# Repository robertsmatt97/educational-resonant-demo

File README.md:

# Educational Demos for Resonant Converter Phenomena

This repository stores all of the project files corresponding to the paper published under the same name. The files are necessary for building, simulating, and operating the converter described in the paper.

## Navigating the Project Files

1. User Manual
    - A detailed guide for setting up and operating the educational board.
    - The User Manual is listed already in the published paper but will be regularly updated here.
    
2. Bill of Materials
    - An Excel spreadsheet that contains every component used for the educational converter.
    - URLs, part numbers, and prices are listed.
    - Mouser cart link attached (To be added) is at the bottom of the spreadsheet for easy purchasing.
    - It is recommended to buy extra parts.
    
3. GERBER Files Zip File
    - A zip file for PCB manufacturers for convenient PCB purchasing.
    - The zip file is suitable for Smart Prototyping, which was used to create the prototype.
    - Some PCB manufacturers require different export options. The User Manual describes how to export it correctly.
    
4. "Videos" Folder
    - Videos demonstrating the capabilities of the converter. 
    - YouTube links are listed below as well. (To be added)
    - Demonstration 1: (To be added)
    - Demonstration 2: (To be added)
    
5. "KiCAD" Folder
    - KiCAD project files containing the schematic and PCB of the converter.
    - Library paths may need to be configured to see symbols and footprints correctly.
    
6. "MATLAB" Folder
    - MATLAB scripts to show hypothetical, simulation, and converter data over different combinations of resonant converter design parameters.
    - 'Resonant_Design.m' shows hypothetical and simulation data only. The board does not need to be connected.
    - 'Resonant_Design_Serial.m' shows hypothetical, simulation, and converter data. The board needs to be connected, and the CCS script needs to be running.
    - MATLAB 2019b or higher is required to run the 'Resonant_Design_Serial.m' script. 
    
7. "LTSpice" Folder
    - Simulation files for the resonant converter. 
    - Configure the parameters where it is listed.
    - Follow the User Manual for instructions on additional operation.
    
8. "CCS" Folder
    - Code Composer Studio (CCS) project files containing the code needed for operation. 
    - The latest version of CCS is recommended for the converter to work.

## To-Do List

1. Add Mouser Cart link of all the components. 
2. Add YouTube links of video demonstrations.
3. Add more visuals to User Manual.
3. Add additional microcontroller features to shorten downtime for demonstrations.

## Contact Information for Help

You can contact me at my email below for assistance in getting the board to work. Please be detailed in your issues.
Email: robertsmatt97@gmail.com

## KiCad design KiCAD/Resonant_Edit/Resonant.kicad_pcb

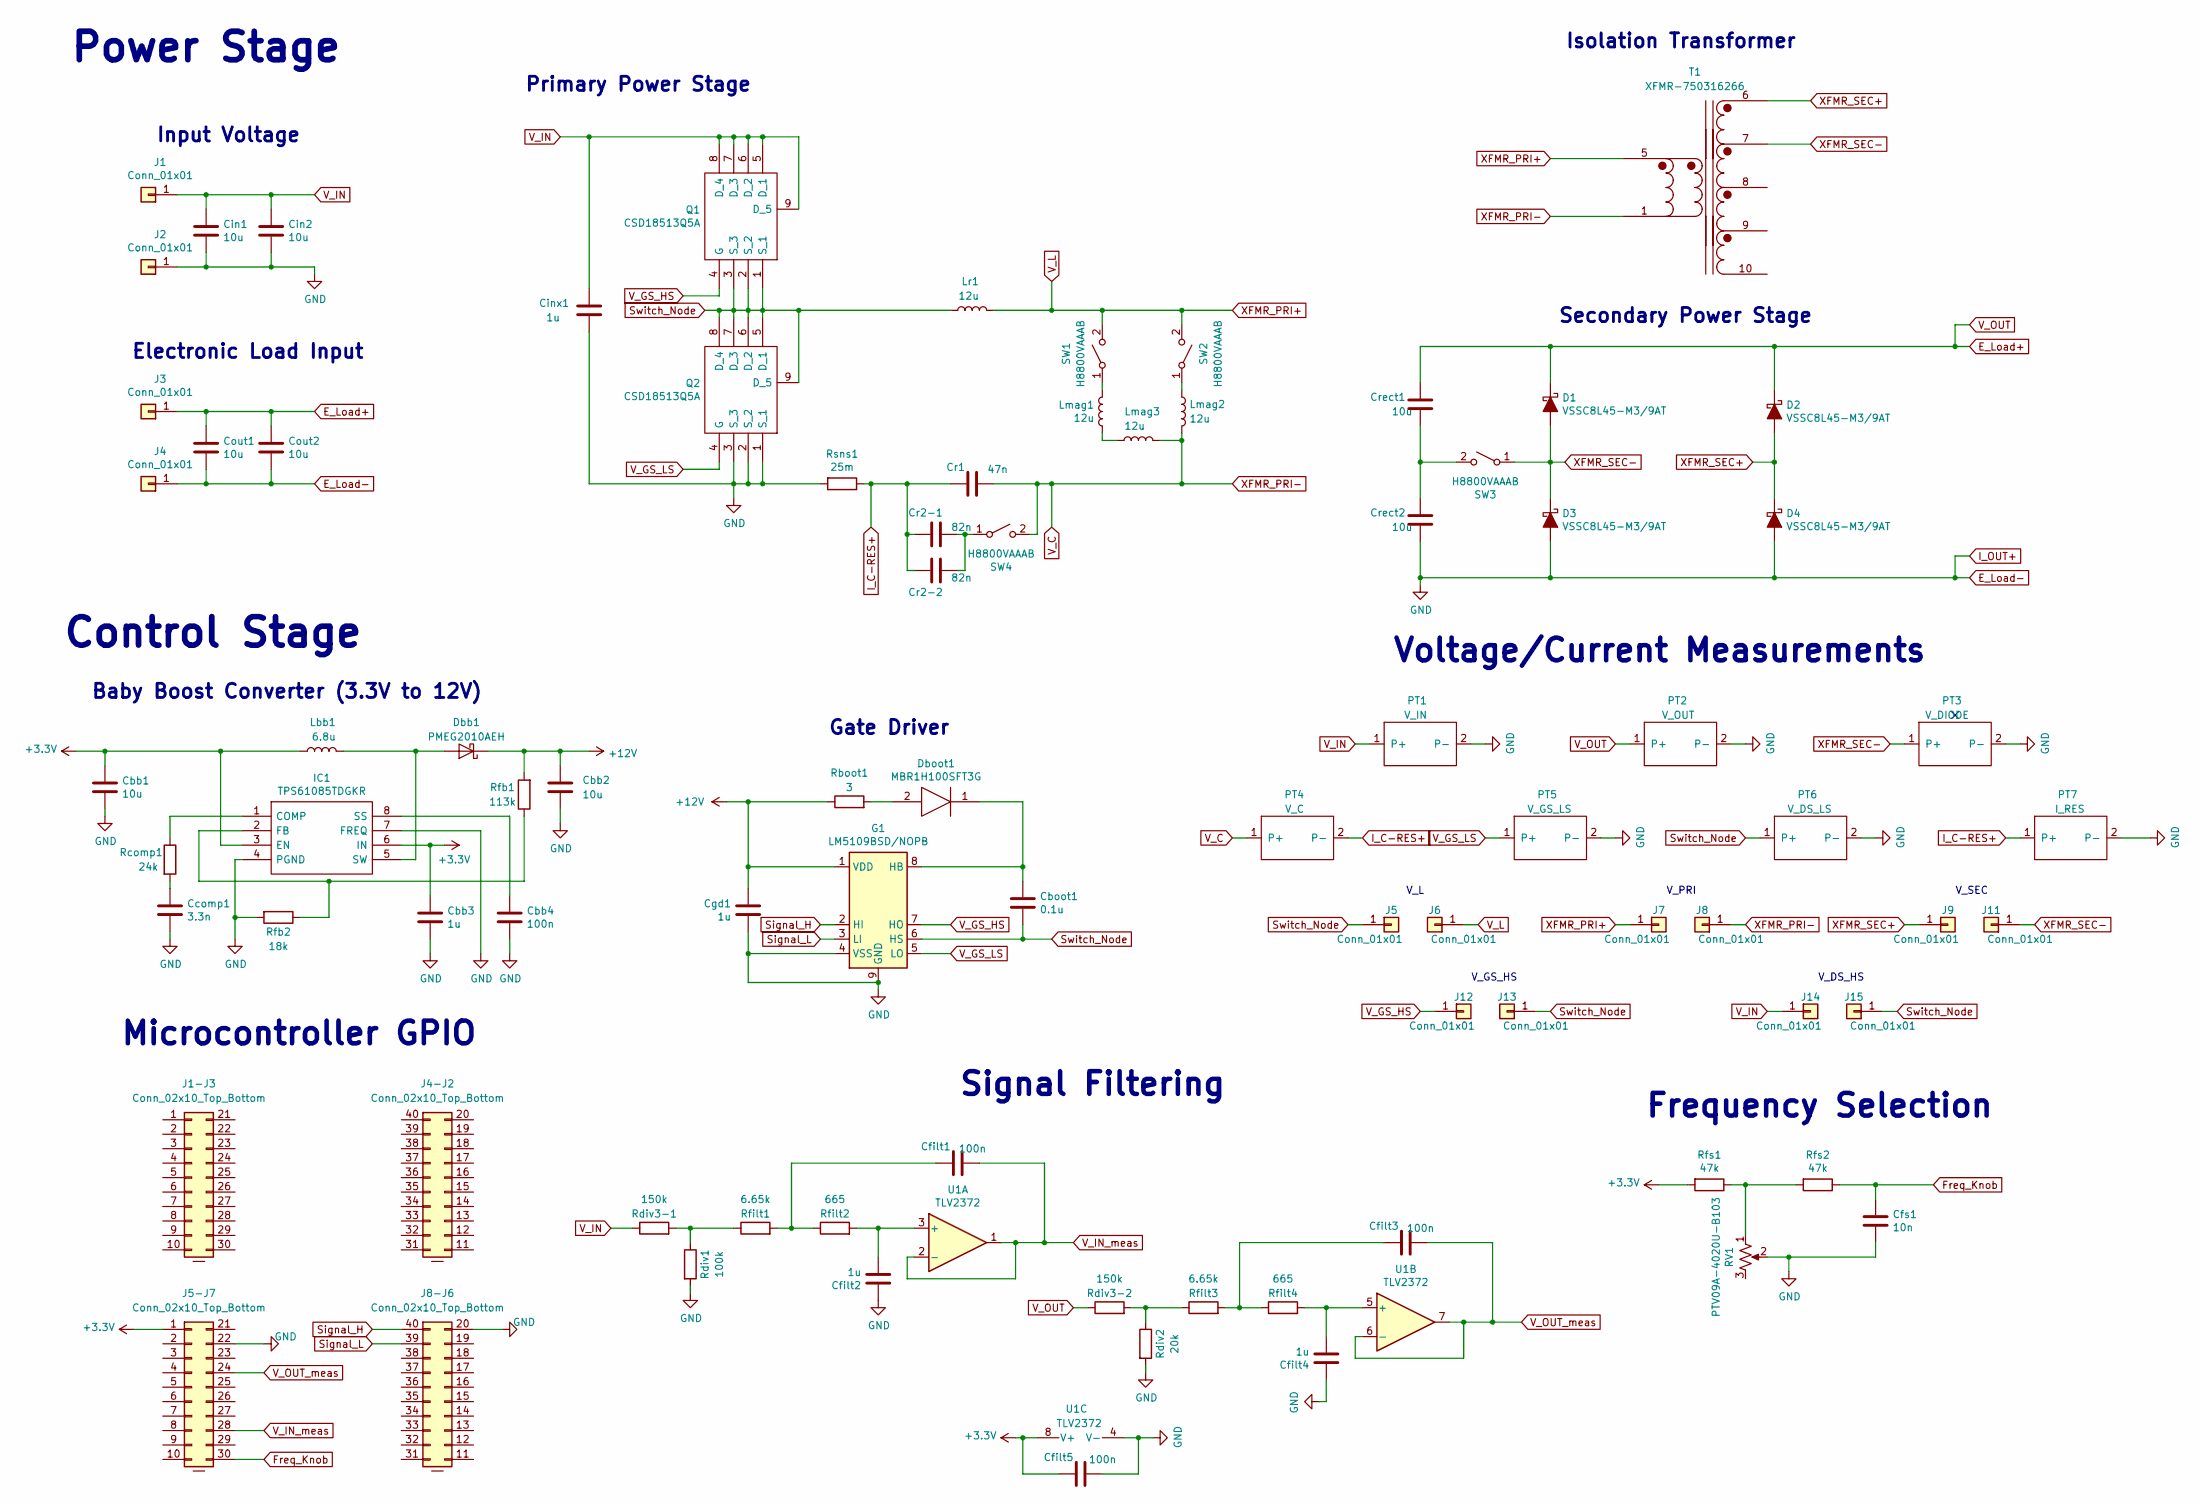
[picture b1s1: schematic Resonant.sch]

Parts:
Cbb1, Cbb2: 10u; C_0603_1608Metric
Cbb3: 1u; C_0603_1608Metric
Cbb4: 100n; C_0603_1608Metric
Cboot1: 0.1u; C_0603_1608Metric
Ccomp1: 3.3n; C_0805_2012Metric
Cfilt1, Cfilt3, Cfilt5: 100n; C_0603_1608Metric
Cfilt2, Cfilt4: 1u; C_0603_1608Metric
Cfs1: 10n; C_0603_1608Metric
Cgd1: 1u; C_0603_1608Metric
Cin1, Cin2: 10u; C_0603_1608Metric
Cinx1: 1u; LLL31MR71C105MA01L
Cout1, Cout2: 10u; C_0603_1608Metric
Cr1: 47n; C_0805_2012Metric
Cr2-1, Cr2-2: 82n; C_1206_3216Metric
Crect1, Crect2: 10u; C_0603_1608Metric
D1, D2, D3, D4: VSSC8L45-M3/9AT; VSSC8L45-M3_9AT
Dbb1: PMEG2010AEH; D_SOD-123
Dboot1: MBR1H100SFT3G; Mouser Part Number 863-MBR1H100SFT3G
G1: LM5109BSD/NOPB; LM5109BSD_NOPB
IC1: TPS61085TDGKR; Mouser Part Number 595-TPS61085TDGKR
J1, J2, J3, J4, J5, J6, J7, J8, J9, J11, J12, J13, J14, J15: Conn_01x01; PinHeader_1x01_P2.54mm_Vertical
J1-J3, J5-J7: Conn_02x10_Top_Bottom; 90151-2320_J1
J4-J2, J8-J6: Conn_02x10_Top_Bottom; 90151-2320_J2
Lbb1: 6.8u; L_0805_2012Metric
Lmag1, Lmag2, Lmag3: 12u; 744373965120
Lr1: 12u; 744373965120
PT1: V_IN; Probe_Test
PT2: V_OUT; Probe_Test
PT3: V_DIODE; Probe_Test
PT4: V_C; Probe_Test
PT5: V_GS_LS; Probe_Test
PT6: V_DS_LS; Probe_Test
PT7: I_RES; Probe_Test
Q1, Q2: CSD18513Q5A; Mouser Part Number 595-CSD18513Q5A
RV1: PTV09A-4020U-B103
Rboot1: 3; R_0603_1608Metric
Rcomp1: 24k; R_0603_1608Metric
Rdiv1: 100k; R_0603_1608Metric
Rdiv2: 20k; R_0603_1608Metric
Rdiv3-1, Rdiv3-2: 150k; R_0603_1608Metric
Rfb1: 113k; R_0805_2012Metric
Rfb2: 18k; R_0805_2012Metric
Rfilt1, Rfilt3: 6.65k; R_0603_1608Metric
Rfilt2, Rfilt4: 665; R_0603_1608Metric
Rfs1, Rfs2: 47k; R_0603_1608Metric
Rsns1: 25m; R_0612_1632Metric
SW1, SW2, SW3, SW4: H8800VAAAB
T1: XFMR-750316266; 750342864
U1: TLV2372; TLV2632

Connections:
+3V3: Cbb1.1, Cbb3.1, Cfilt5.1, IC1.3 (EN), IC1.6 (IN), J5-J7.1, Lbb1.1, Rfs1.2, U1.8 (V+)
+12V: Cbb2.2, Cgd1.1, Dbb1.1 (K), G1.1 (VDD), Rboot1.1, Rfb1.2
E_Load+: Cout1.1, Cout2.1, Crect1.1, D1.1 (K), D2.1 (K), J3.1, PT2.1 (P+), Rdiv3-2.1
E_Load-: Cbb1.2, Cbb2.1, Cbb3.2, Cbb4.2, Ccomp1.2, Cfilt2.1, Cfilt4.1, Cfilt5.2, Cfs1.2, Cgd1.2, Cin1.2, Cin2.2, Cinx1.2, Cout1.2, Cout2.2, Crect2.2, D3.2 (A), D4.2 (A), G1.4 (VSS), G1.9 (GND), IC1.4 (PGND), IC1.7 (FREQ), J2.1, J4.1, J5-J7.22 (Pin_12), J8-J6.20 (Pin_11), PT1.2 (P-), PT2.2 (P-), PT3.2 (P-), PT5.2 (P-), PT6.2 (P-), PT7.2 (P-), Q2.1 (S_1), Q2.2 (S_2), Q2.3 (S_3), RV1.2, Rdiv1.2, Rdiv2.2, Rfb2.2, Rsns1.2, U1.4 (V-)
Freq_Knob: Cfs1.1, J5-J7.30 (Pin_20), Rfs2.1
I_C-RES+: Cr1.1, Cr2-1.1, Cr2-2.1, PT4.2 (P-), PT7.1 (P+), Rsns1.1
unnamed: Cbb4.1, IC1.8 (SS)
unnamed: Cboot1.1, Dboot1.1, G1.8 (HB)
unnamed: Ccomp1.1, Rcomp1.2
unnamed: Cfilt1.1, Rfilt1.2, Rfilt2.1
unnamed: Cfilt2.2, Rfilt2.2, U1.3 (+)
unnamed: Cfilt3.1, Rfilt3.2, Rfilt4.1
unnamed: Cfilt4.2, Rfilt4.2, U1.5 (+)
unnamed: Cr2-1.2, Cr2-2.2, SW4.1 (A)
unnamed: Crect1.2, Crect2.1, SW3.2 (B)
unnamed: Dbb1.2 (A), IC1.5 (SW), Lbb1.2
unnamed: Dboot1.2, Rboot1.2
unnamed: IC1.1 (COMP), Rcomp1.1
unnamed: IC1.2 (FB), Rfb1.1, Rfb2.1
unnamed: Lmag1.1, SW1.1 (A)
unnamed: Lmag1.2, Lmag3.2
unnamed: Lmag2.2, SW2.1 (A)
unnamed: RV1.1, Rfs1.1, Rfs2.2
unnamed: Rdiv1.1, Rdiv3-1.2, Rfilt1.1
unnamed: Rdiv2.1, Rdiv3-2.2, Rfilt3.1
Signal_H: G1.2 (HI), J8-J6.40 (Pin_1)
Signal_L: G1.3 (LI), J8-J6.39 (Pin_2)
Switch_Node: Cboot1.2, G1.6 (HS), J5.1, J13.1, J15.1, Lr1.1, PT6.1 (P+), Q1.1 (S_1), Q1.2 (S_2), Q1.3 (S_3), Q2.5 (D_1), Q2.6 (D_2), Q2.7 (D_3), Q2.8 (D_4), Q2.9 (D_5)
V_C: Cr1.2, J8.1, Lmag2.1, Lmag3.1, PT4.1 (P+), SW4.2 (B), T1.1 (AB)
V_GS_HS: G1.7 (HO), J12.1, Q1.4 (G)
V_GS_LS: G1.5 (LO), PT5.1 (P+), Q2.4 (G)
V_IN: Cin1.1, Cin2.1, Cinx1.1, J1.1, J14.1, PT1.1 (P+), Q1.5 (D_1), Q1.6 (D_2), Q1.7 (D_3), Q1.8 (D_4), Q1.9 (D_5), Rdiv3-1.1
V_IN_meas: Cfilt1.2, J5-J7.28 (Pin_18), U1.1, U1.2 (-)
V_L: J6.1, J7.1, Lr1.2, SW1.2 (B), SW2.2 (B), T1.5 (AA)
V_OUT_meas: Cfilt3.2, J5-J7.24 (Pin_14), U1.6 (-), U1.7
XFMR_SEC+: D2.2 (A), D4.1 (K), J9.1, T1.6 (SB)
XFMR_SEC-: D1.2 (A), D3.1 (K), J11.1, PT3.1 (P+), SW3.1 (A), T1.7 (SC)

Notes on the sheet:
Primary Power Stage
Secondary Power Stage
Gate Driver
Input Voltage
Baby Boost Converter (3.3V to 12V)
Control Stage
Microcontroller GPIO
Power Stage
Electronic Load Input
Isolation Transformer
Frequency Selection
Signal Filtering
Voltage/Current Measurements
V_L
V_SEC
V_PRI
V_DS_HS
V_GS_HS

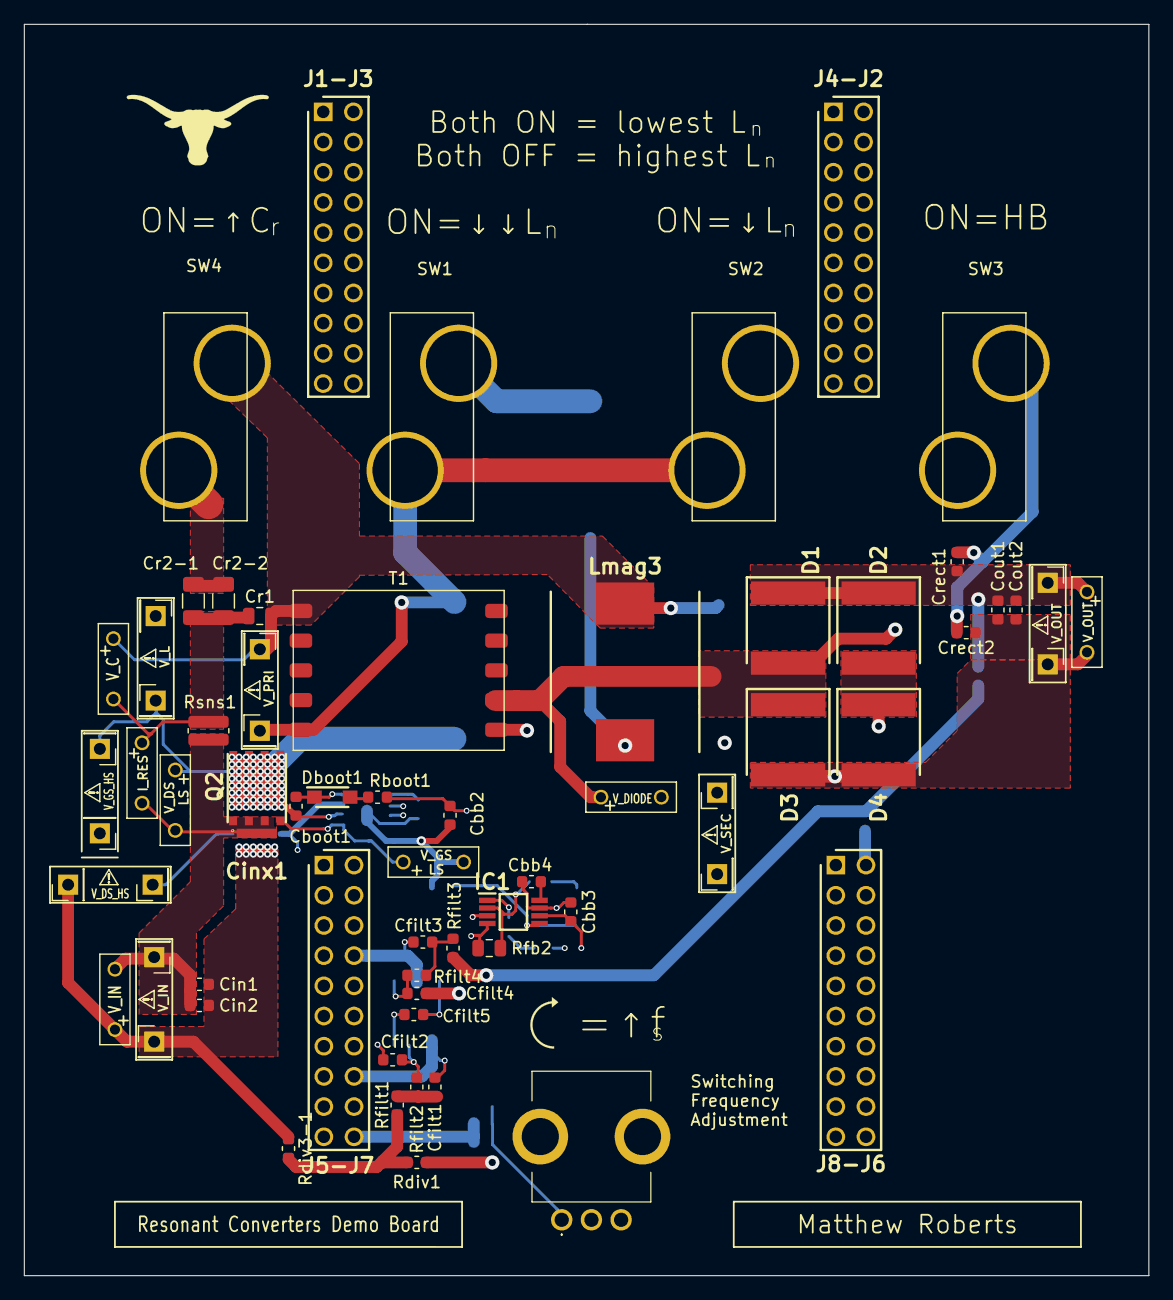
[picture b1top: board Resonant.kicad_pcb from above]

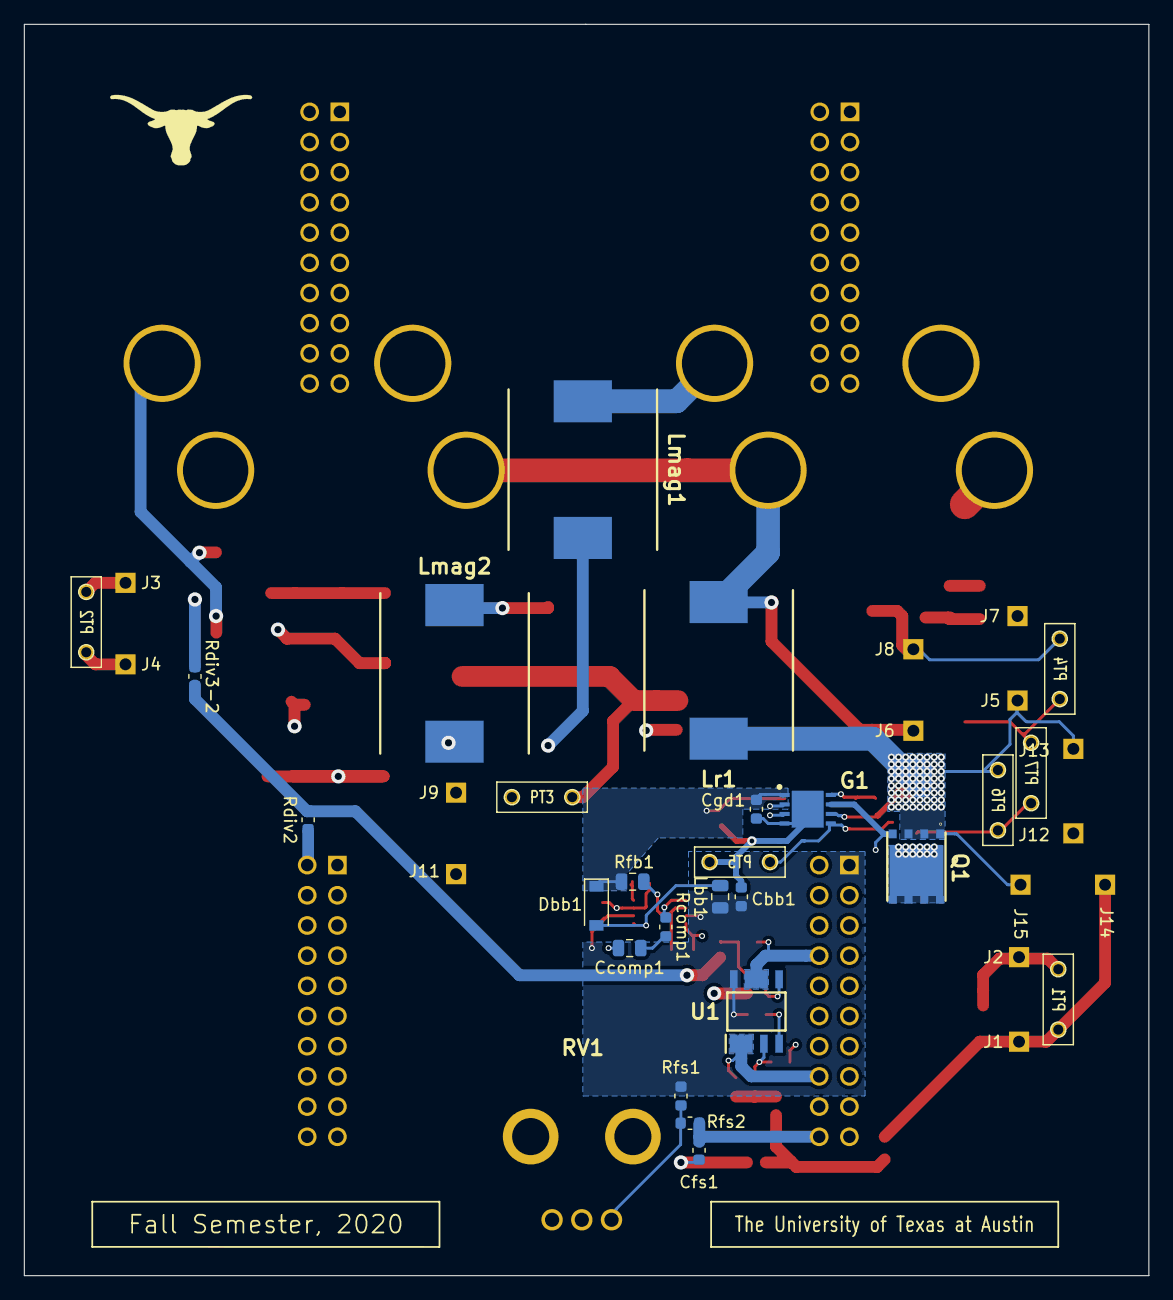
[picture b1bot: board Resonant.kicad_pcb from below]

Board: 4 copper layers, 94.6 x 105.3 mm, 85 parts (18 on the bottom side), 37 nets.

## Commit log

2020-12-04 Added initial documents
    First Commit
2020-12-05 Added BOM
    Added the Bill of Materials of the Converter
2020-12-05 Added Videos
    Added Demonstration Videos
2020-12-06 Final 2020 changes to files
2020-12-06 Added User Manual
